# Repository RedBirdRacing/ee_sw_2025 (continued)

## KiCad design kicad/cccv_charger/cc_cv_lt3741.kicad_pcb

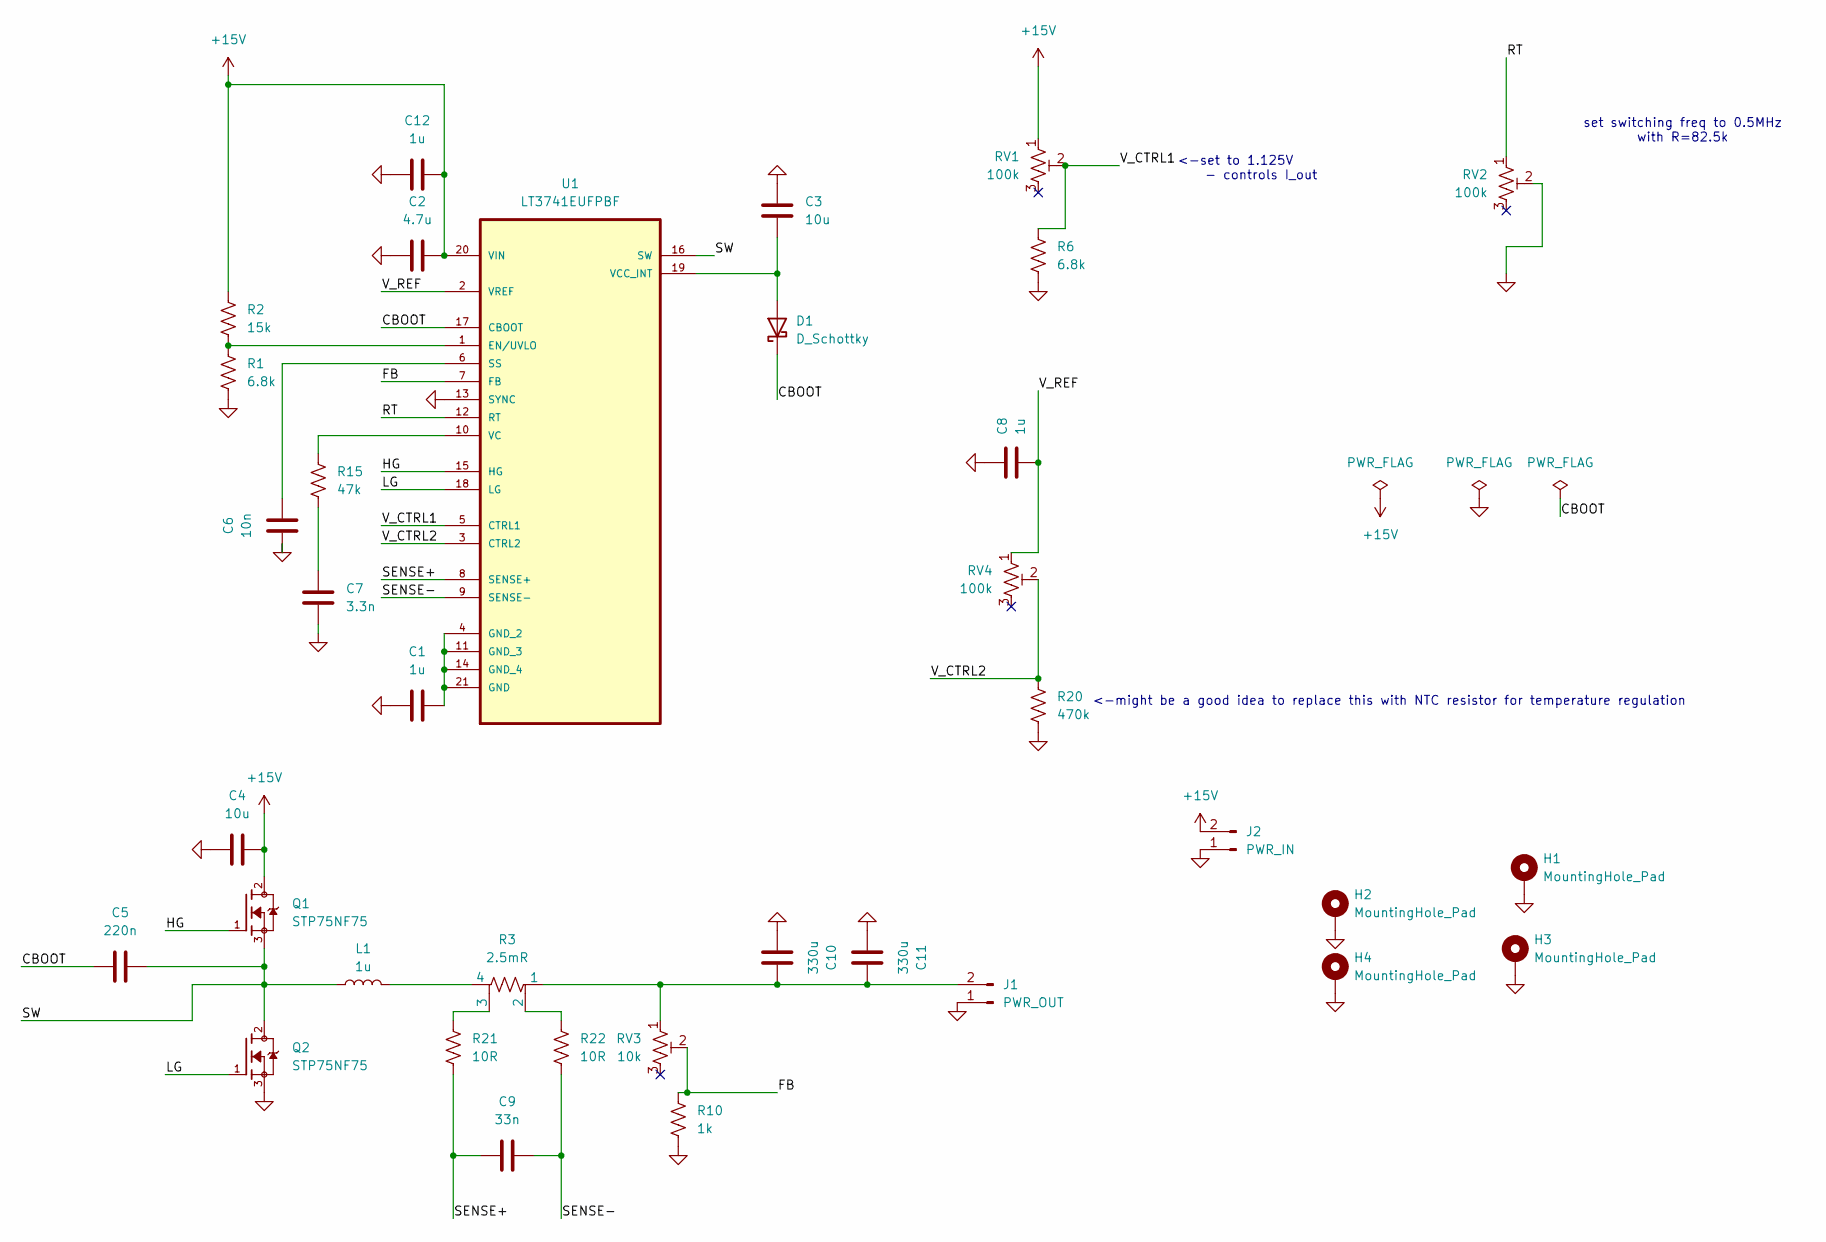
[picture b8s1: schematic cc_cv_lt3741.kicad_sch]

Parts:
C1, C8, C12: 1u; C_0805_2012Metric_Pad1.18x1.45mm_HandSolder
C2: 4.7u; C_0805_2012Metric_Pad1.18x1.45mm_HandSolder
C3, C4: 10u; C_0805_2012Metric_Pad1.18x1.45mm_HandSolder
C5: 220n; C_0805_2012Metric_Pad1.18x1.45mm_HandSolder
C6: 10n; C_0805_2012Metric_Pad1.18x1.45mm_HandSolder
C7: 3.3n; C_0805_2012Metric_Pad1.18x1.45mm_HandSolder
C9: 33n; C_0805_2012Metric_Pad1.18x1.45mm_HandSolder
C10, C11: 330u; C_0805_2012Metric_Pad1.18x1.45mm_HandSolder
D1: D_Schottky; D_T-1_P12.70mm_Horizontal
H1, H2, H3, H4: MountingHole_Pad; MountingHole_2.2mm_M2_Pad_Via
J1: PWR_OUT; AMASS_XT60-M_1x02_P7.20mm_Vertical
J2: PWR_IN; AMASS_XT60-M_1x02_P7.20mm_Vertical
L1: 1u; 1uH_80A_inductor
Q1, Q2: STP75NF75; TO255P1040X460X2890-3; DigiKey_Part_Number 497-2788-5-ND
R1, R6: 6.8k; R_0805_2012Metric_Pad1.20x1.40mm_HandSolder
R2: 15k; R_0805_2012Metric_Pad1.20x1.40mm_HandSolder
R3: 2.5mR; R_Shunt_Ohmite_LVK24
R10: 1k; R_0805_2012Metric_Pad1.20x1.40mm_HandSolder
R15: 47k; R_0805_2012Metric_Pad1.20x1.40mm_HandSolder
R20: 470k; R_0805_2012Metric_Pad1.20x1.40mm_HandSolder
R21, R22: 10R; R_0805_2012Metric_Pad1.20x1.40mm_HandSolder
RV1, RV2, RV4: 100k; Potentiometer_Bourns_3296W_Vertical
RV3: 10k; Potentiometer_Bourns_3296W_Vertical
U1: LT3741EUFPBF; ETSSOP-20-1EP_4.4x6.5mm_P0.65mm_EP3x4.2mm; MPN LT3741EUF#PBF

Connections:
+15V: C2.2, C4.2, C12.2, J2.2, Q1.2, R2.1, RV1.1, U1.20 (VIN)
/CBOOT: C5.1, D1.1 (K), U1.17 (CBOOT)
/FB: R10.1, RV3.2, U1.7 (FB)
/HG: Q1.1, U1.15 (HG)
/LG: Q2.1, U1.18 (LG)
/RT: RV2.1, U1.12 (RT)
/SENSE+: C9.1, R21.2, U1.8 (SENSE+)
/SENSE-: C9.2, R22.2, U1.9 (SENSE-)
/SW: C5.2, L1.1, Q1.3, Q2.2, U1.16 (SW)
/V_CTRL1: R6.1, RV1.2, U1.5 (CTRL1)
/V_CTRL2: R20.1, RV4.2, U1.3 (CTRL2)
/V_REF: C8.2, RV4.1, U1.2 (VREF)
GND: C1.1, C2.1, C3.1, C4.1, C6.1, C7.1, C8.1, C10.1, C11.1, C12.1, H1.1, H2.1, H3.1, H4.1, J1.1, J2.1, Q2.3, R1.2, R6.2, R10.2, R20.2, RV2.2, U1.13 (SYNC)
unnamed: C7.2, R15.2
unnamed: C3.2, D1.2 (A), U1.19 (VCC_INT)
unnamed: C10.2, C11.2, J1.2, R3.1, RV3.1
unnamed: L1.2, R3.4
unnamed: R3.3, R21.1
unnamed: R3.2, R22.1
unnamed: R1.1, R2.2, U1.1 (EN/UVLO)
unnamed: C1.2, U1.4 (GND_2), U1.11 (GND_3), U1.14 (GND_4), U1.21 (GND)
unnamed: C6.2, U1.6 (SS)
unnamed: R15.1, U1.10 (VC)

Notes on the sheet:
<-set to 1.125V - controls I_out
set switching freq to 0.5MHz with R=82.5k
<-might be a good idea to replace this with NTC resistor for temperature regulation

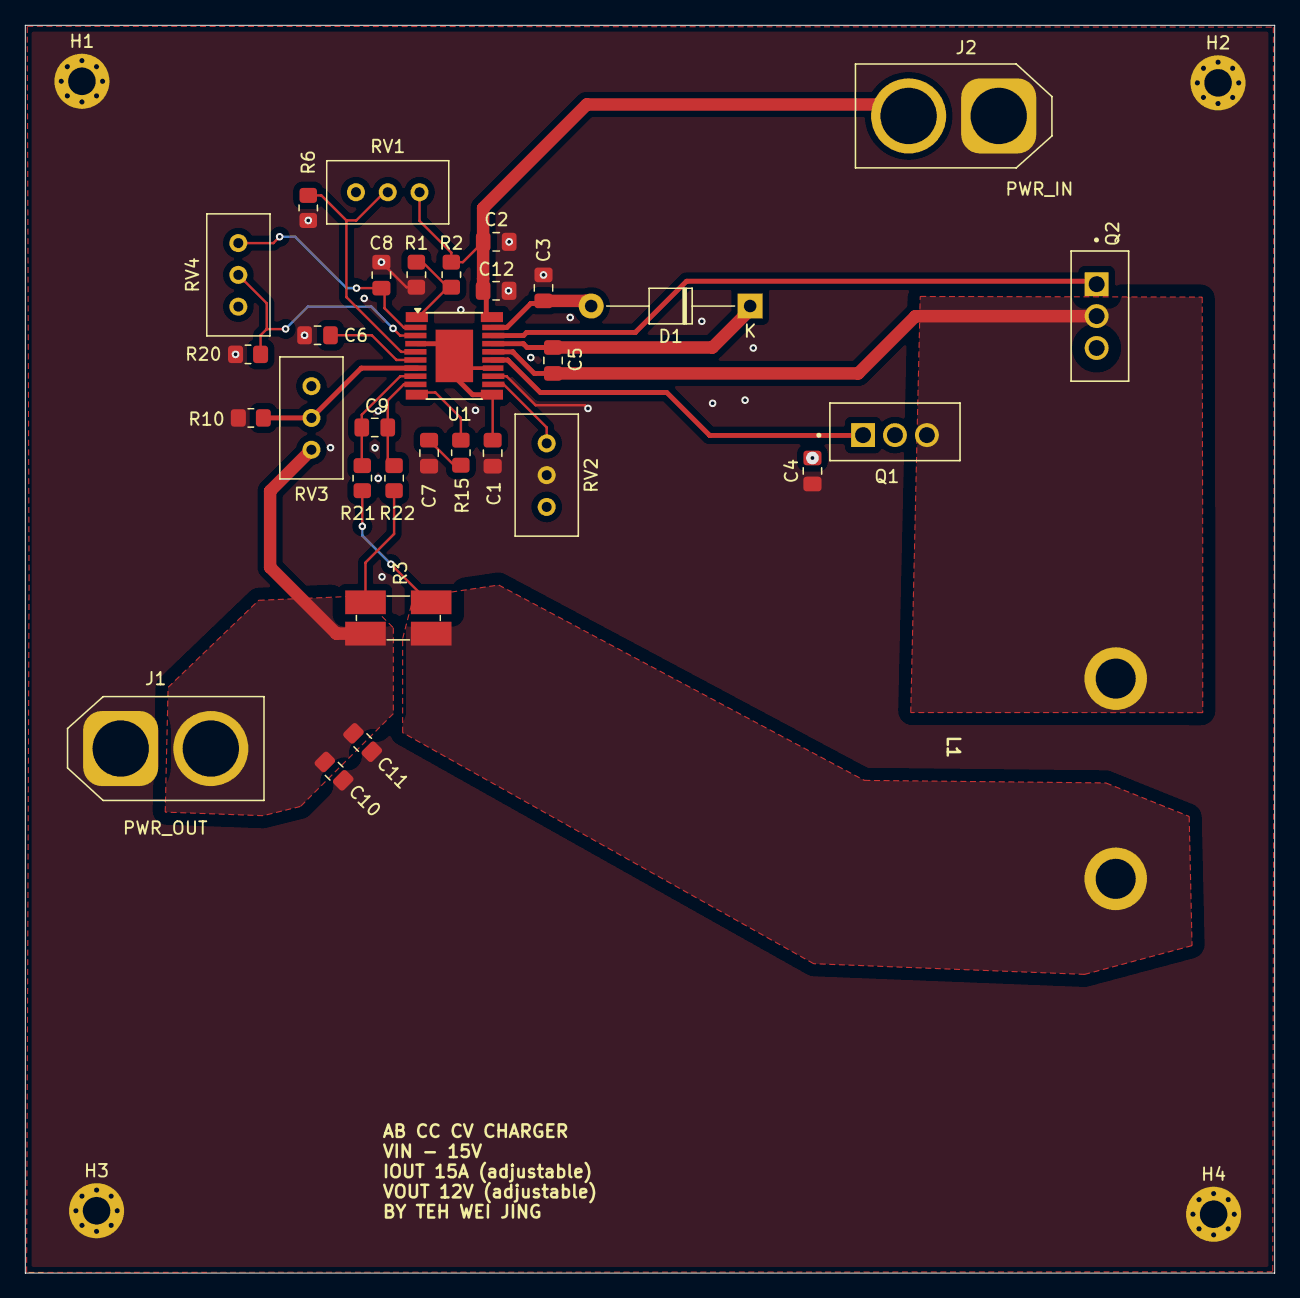
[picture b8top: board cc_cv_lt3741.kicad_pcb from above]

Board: 2 copper layers, 99.8 x 99.7 mm, 36 parts (0 on the bottom side), 23 nets.
